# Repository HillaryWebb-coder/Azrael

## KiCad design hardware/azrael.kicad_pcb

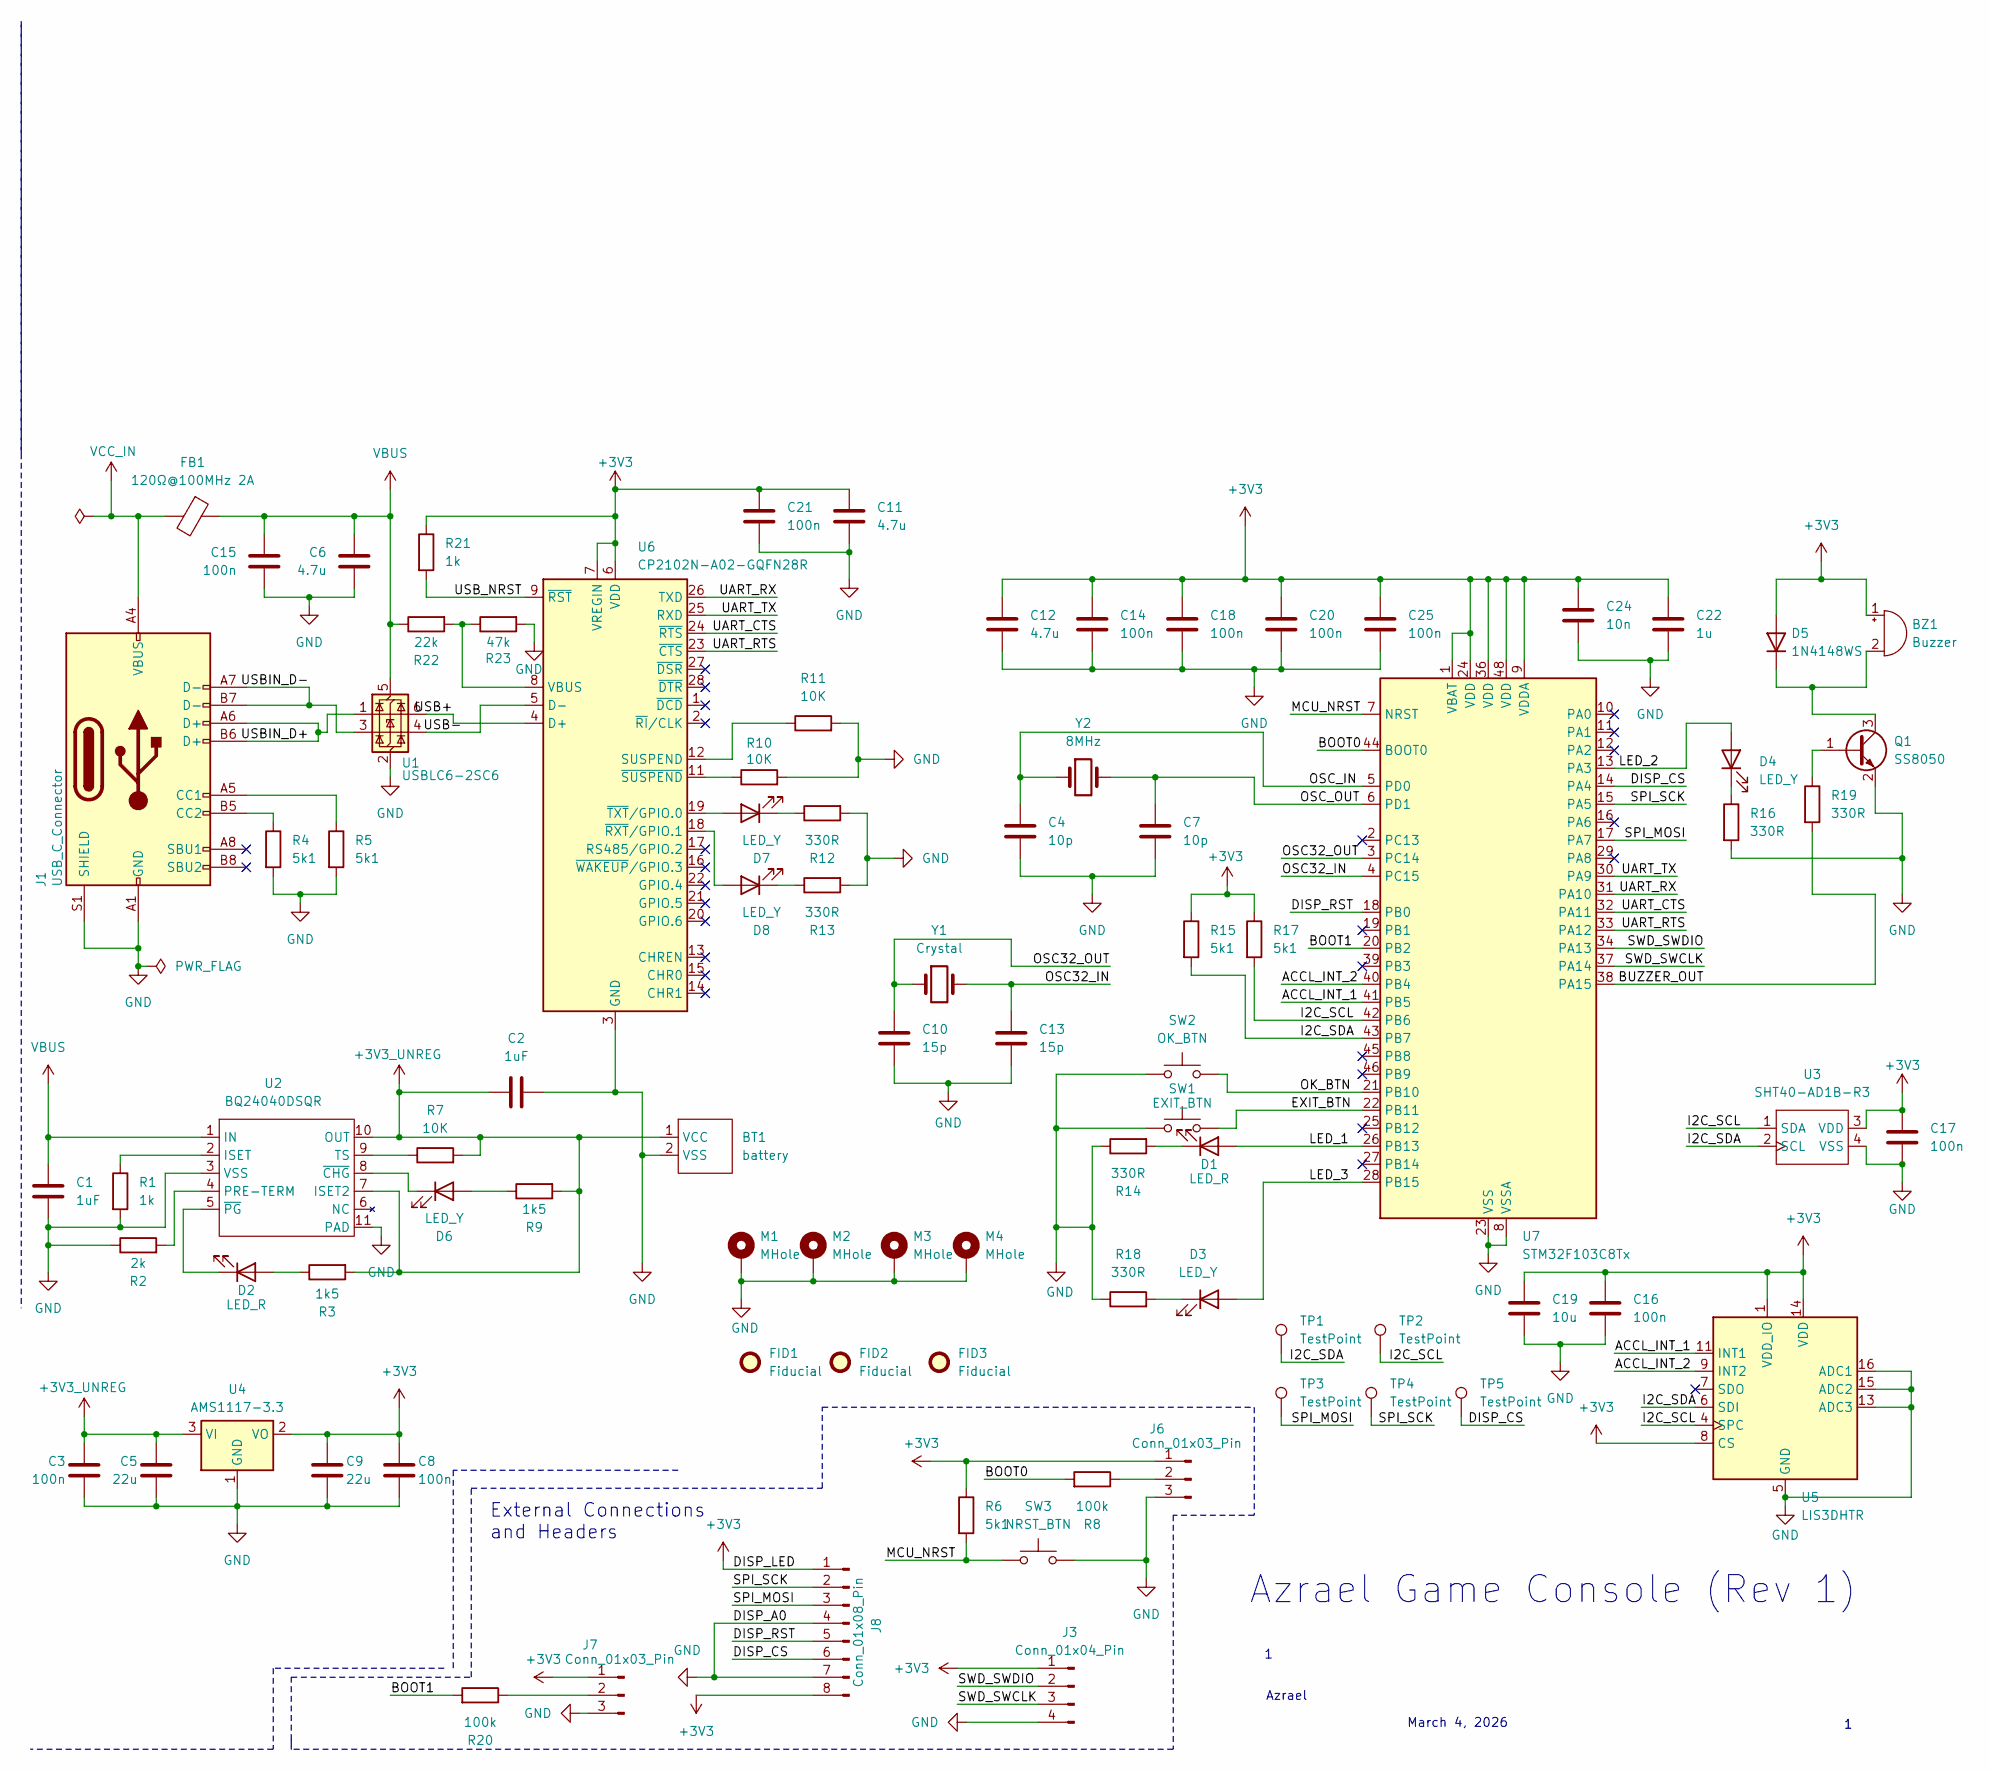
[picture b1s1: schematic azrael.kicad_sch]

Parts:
BT1: battery; SolderWire-0.5sqmm_1x02_P4.6mm_D0.9mm_OD2.1mm_Relief
BZ1: Buzzer; SolderWire-0.1sqmm_1x02_P3.6mm_D0.4mm_OD1mm_Relief
C1, C2: 1uF; C_0603_1608Metric_Pad1.08x0.95mm_HandSolder; MFR.Part # CL05A105KA5NQNC; JLCPCB Part # C52923
C3, C8, C14, C15, C16, C17, C18, C20, C21, C25: 100n; C_0402_1005Metric_Pad0.74x0.62mm_HandSolder; MFR.Part # CL05B104KO5NNNC; JLCPCB Part # C1525
C4, C7: 10p; C_0603_1608Metric_Pad1.08x0.95mm_HandSolder; MFR.Part # CL10C100JB8NNNC; JLCPCB Part # C1634
C5, C9: 22u; C_1206_3216Metric_Pad1.33x1.80mm_HandSolder; MFR.Part # CL31A226KAHNNNE; JLCPCB Part # C12891
C6, C11, C12: 4.7u; C_0805_2012Metric_Pad1.18x1.45mm_HandSolder; MFR.Part # CL21A475KAQNNNE; JLCPCB Part # C1779
C10, C13: 15p; C_0603_1608Metric_Pad1.08x0.95mm_HandSolder; MFR.Part # CL10C150JB8NNNC; JLCPCB Part # C1644
C19: 10u; C_0603_1608Metric_Pad1.08x0.95mm_HandSolder; MFR.Part # CL10A106MA8NRNC; JLCPCB Part # C96446
C22: 1u; C_0603_1608Metric_Pad1.08x0.95mm_HandSolder; MFR.Part # CL05A105KA5NQNC; JLCPCB Part # C52923
C24: 10n; C_0805_2012Metric_Pad1.18x1.45mm_HandSolder; MFR.Part # CL21B103KBANNNC; JLCPCB Part # C1710
D1, D2: LED_R; LED_0603_1608Metric_Pad1.05x0.95mm_HandSolder; MFR.Part # KT-0603R; JLCPCB Part # C2286
D3, D7, D8: LED_Y; LED_0805_2012Metric_Pad1.15x1.40mm_HandSolder; MFR.Part # KT-0805Y; JLCPCB Part # C2296
D4, D6: LED_Y; LED_0805_2012Metric_Pad1.15x1.40mm_HandSolder; MFR.Part # KT-0805G; JLCPCB Part # C2297
D5: 1N4148WS; D_SOD-323; MFR.Part # 1N4148WS; JLCPCB Part # C2128
FB1: 120Ω@100MHz 2A; L_0603_1608Metric; MFR.Part # BLM18PG121SN1D; JLCPCB Part # C14709
FID1, FID2, FID3: Fiducial; Fiducial_1.5mm_Mask3mm
J1: USB_C_Connector; USB_C_Receptacle_GCT_USB4105-xx-A_16P_TopMnt_Horizontal; MFR.Part # TYPE-C 16PIN 2MD(073); JLCPCB Part # C2765186
J3: Conn_01x04_Pin; JST_PH_B4B-PH-K_1x04_P2.00mm_Vertical
J6, J7: Conn_01x03_Pin; PinHeader_1x03_P2.54mm_Vertical
J8: Conn_01x08_Pin; JST_PH_B8B-PH-K_1x08_P2.00mm_Vertical
M1, M2, M3, M4: MHole; MountingHole_3.2mm_M3_Pad_Via
Q1: SS8050; SOT-23; MFR.Part # SS8050(RANGE:200-350); JLCPCB Part # C2150
R1, R21: 1k; R_0603_1608Metric_Pad0.98x0.95mm_HandSolder; MFR.Part # 0603WAF1001T5E; JLCPCB Part # C21190
R2: 2k; R_0603_1608Metric_Pad0.98x0.95mm_HandSolder; MFR.Part # 0603WAF2001T5E; JLCPCB Part # C22975
R3, R9: 1k5; R_0603_1608Metric_Pad0.98x0.95mm_HandSolder; MFR.Part # 0603WAF1501T5E; JLCPCB Part # C22843
R4, R5, R6, R15, R17: 5k1; R_0603_1608Metric_Pad0.98x0.95mm_HandSolder; MFR.Part # 0603WAF5101T5E; JLCPCB Part # C23186
R7, R10, R11: 10K; R_0603_1608Metric_Pad0.98x0.95mm_HandSolder; MFR.Part # 0603WAF1002T5E; JLCPCB Part # C25804
R8, R20: 100k; R_0603_1608Metric_Pad0.98x0.95mm_HandSolder; MFR.Part # 0603WAF1003T5E; JLCPCB Part # C25803
R12, R13, R14, R16, R18, R19: 330R; R_0603_1608Metric_Pad0.98x0.95mm_HandSolder; MFR.Part # 0603WAF3300T5E; JLCPCB Part # C23138
R22: 22k; R_0603_1608Metric_Pad0.98x0.95mm_HandSolder; MFR.Part # 0603WAF2202T5E; JLCPCB Part # C31850
R23: 47k; R_0603_1608Metric_Pad0.98x0.95mm_HandSolder; MFR.Part # 0603WAF4702T5E; JLCPCB Part # C25819
SW1: EXIT_BTN; SW_Push_SPST_NO_Alps_SKRK; MFR.Part # TS-1088-AR02016; JLCPCB Part # C720477
SW2: OK_BTN; SW_Push_SPST_NO_Alps_SKRK; MFR.Part # TS-1088-AR02016; JLCPCB Part # C720477
SW3: NRST_BTN; SW_Push_SPST_NO_Alps_SKRK; MFR.Part # TS-1088-AR02016; JLCPCB Part # C720477
TP1, TP2, TP3, TP4, TP5: TestPoint; TestPoint_Pad_D1.0mm
U1: USBLC6-2SC6; SOT-23-6
U2: BQ24040DSQR; Texas_DSQ0010A_WSON-10-1EP_2x2mm_P0.4mm_EP0.9x1.5mm_Thermal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; MFR.Part # BQ24040DSQR; JLCPCB Part # C81080
U3: SHT40-AD1B-R3; Sensirion_DFN-4_1.5x1.5mm_P0.8mm_SHT4x_NoCentralPad; MFR.Part # SHT40-AD1B-R3; JLCPCB Part # C2848306
U4: AMS1117-3.3; SOT-223-3_TabPin2; MFR.Part # AMS1117-3.3; JLCPCB Part # C6186
U5: LIS3DHTR; LGA-16_3x3mm_P0.5mm_LayoutBorder3x5y; MFR.Part # LIS3DHTR; JLCPCB Part # C15134
U6: CP2102N-A02-GQFN28R; QFN-28-1EP_5x5mm_P0.5mm_EP3.35x3.35mm; MFR.Part # CP2102N-A02-GQFN28R; JLCPCB Part # C964632
U7: STM32F103C8Tx; LQFP-48_7x7mm_P0.5mm
Y1: Crystal; Crystal_SMD_3215-2Pin_3.2x1.5mm; MFR.Part # Q13FC13500004; JLCPCB Part # C32346
Y2: 8MHz; Crystal_SMD_5032-2Pin_5.0x3.2mm_HandSoldering; MFR.Part # X50328MSB2GI; JLCPCB Part # C115962

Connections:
+3V3: BZ1.1 (+), C8.1, C9.1, C11.1, C12.1, C14.1, C16.1, C17.1, C18.1, C19.1, C20.1, C21.1, C22.1, C24.1, C25.1, D5.2 (A), J3.1, J6.1, J7.1, J8.1, J8.8, R6.1, R15.1, R17.1, R21.1, U3.3 (VDD), U4.2 (VO), U5.1 (VDD_IO), U5.8 (CS), U5.14 (VDD), U6.6 (VDD), U6.7 (VREGIN), U7.1 (VBAT), U7.9 (VDDA), U7.24 (VDD), U7.36 (VDD), U7.48 (VDD)
+3V3_UNREG: BT1.1 (VCC), C2.1, C3.1, C5.1, R3.2, R7.2, R9.2, U2.7 (ISET2), U2.10 (OUT), U4.3 (VI)
/ACCL_INT_1: U5.11 (INT1), U7.41 (PB5)
/ACCL_INT_2: U5.9 (INT2), U7.40 (PB4)
/BOOT0: R8.2, U7.44 (BOOT0)
/BOOT1: R20.2, U7.20 (PB2)
/BUZZER_OUT: R19.2, U7.38 (PA15)
/DISP_CS: J8.6, TP5.1, U7.14 (PA4)
/DISP_RST: J8.5, U7.18 (PB0)
/EXIT_BTN: SW1.2, U7.22 (PB11)
/I2C_SCL: R17.2, TP2.1, U3.1 (SDA), U5.4 (SPC), U7.42 (PB6)
/I2C_SDA: R15.2, TP1.1, U3.2 (SCL), U5.6 (SDI), U7.43 (PB7)
/LED_1: D1.2 (A), U7.26 (PB13)
/LED_2: D4.2 (A), U7.13 (PA3)
/LED_3: D3.2 (A), U7.28 (PB15)
/MCU_NRST: R6.2, SW3.1, U7.7 (NRST)
/OK_BTN: SW2.2, U7.21 (PB10)
/OSC32_IN: C13.1, U7.4 (PC15), Y1.2
/OSC32_OUT: C10.1, U7.3 (PC14), Y1.1
/OSC_IN: C4.1, U7.5 (PD0), Y2.1
/OSC_OUT: C7.1, U7.6 (PD1), Y2.2
/SPI_MOSI: J8.3, TP3.1, U7.17 (PA7)
/SPI_SCK: J8.2, TP4.1, U7.15 (PA5)
/SWD_SWCLK: J3.3, U7.37 (PA14)
/SWD_SWDIO: J3.2, U7.34 (PA13)
/UART_CTS: U6.24 (~RTS), U7.32 (PA11)
/UART_RTS: U6.23 (~CTS), U7.33 (PA12)
/UART_RX: U6.26 (TXD), U7.31 (PA10)
/UART_TX: U6.25 (RXD), U7.30 (PA9)
/USB+: U1.6 (I/O1), U6.4 (D+)
/USB-: U1.4 (I/O2), U6.5 (D-)
/USBIN_D+: J1.A6 (D+), J1.B6 (D+), U1.1 (I/O1)
/USBIN_D-: J1.A7 (D-), J1.B7 (D-), U1.3 (I/O2)
/USB_NRST: R21.2, U6.9 (~RST)
GND: BT1.2 (VSS), C1.2, C2.2, C3.2, C4.2, C5.2, C6.2, C7.2, C8.2, C9.2, C10.2, C11.2, C12.2, C13.2, C14.2, C15.2, C16.2, C17.2, C18.2, C19.2, C20.2, C21.2, C22.2, C24.2, C25.2, J1.A1 (GND), J1.A12 (GND), J1.B1 (GND), J1.B12 (GND), J1.S1 (SHIELD), J3.4, J6.3, J7.3, J8.4, J8.7, M1.1, M2.1, M3.1, M4.1, Q1.2 (E), R1.2, R2.1, R4.2, R5.2, R10.2, R11.2, R12.2, R13.2, R14.1, R16.2, R18.1, R23.2, SW1.1, SW2.1, SW3.2, U1.2 (GND), U2.3 (VSS), U2.11 (PAD), U3.4 (VSS), U4.1 (GND), U5.5 (GND), U5.10 (GND), U5.12 (GND), U5.13 (ADC3), U5.15 (ADC2), U5.16 (ADC1), U6.3 (GND), U6.29 (GND), U7.8 (VSSA), U7.23 (VSS), U7.35 (VSS), U7.47 (VSS)
unnamed: BZ1.2 (-), D5.1 (K), Q1.3 (C)
unnamed: D1.1 (K), R14.2
unnamed: D2.2 (A), R3.1
unnamed: D2.1 (K), U2.5 (~PG)
unnamed: D3.1 (K), R18.2
unnamed: D4.1 (K), R16.1
unnamed: D6.2 (A), R9.1
unnamed: D6.1 (K), U2.8 (~CHG)
unnamed: D7.2 (A), U6.19 (~TXT/GPIO.0)
unnamed: D7.1 (K), R12.1
unnamed: D8.2 (A), U6.18 (~RXT/GPIO.1)
unnamed: D8.1 (K), R13.1
unnamed: J1.A5 (CC1), R5.1
unnamed: J1.B5 (CC2), R4.1
unnamed: J6.2, R8.1
unnamed: J7.2, R20.1
unnamed: Q1.1 (B), R19.1
unnamed: R1.1, U2.2 (ISET)
unnamed: R2.2, U2.4 (PRE-TERM)
unnamed: R7.1, U2.9 (TS)
unnamed: R11.1, U6.12 (SUSPEND)
unnamed: R22.2, R23.1, U6.8 (VBUS)
unnamed: R10.1, U6.11 (~SUSPEND)
VBUS: C1.1, C6.1, C15.1, FB1.1, R22.1, U1.5 (VBUS), U2.1 (IN)
VCC_IN: FB1.2, J1.A4 (VBUS), J1.A9 (VBUS), J1.B4 (VBUS), J1.B9 (VBUS)

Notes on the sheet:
Azrael
Azrael Game Console (Rev 1)
External Connections and Headers
March 4, 2026

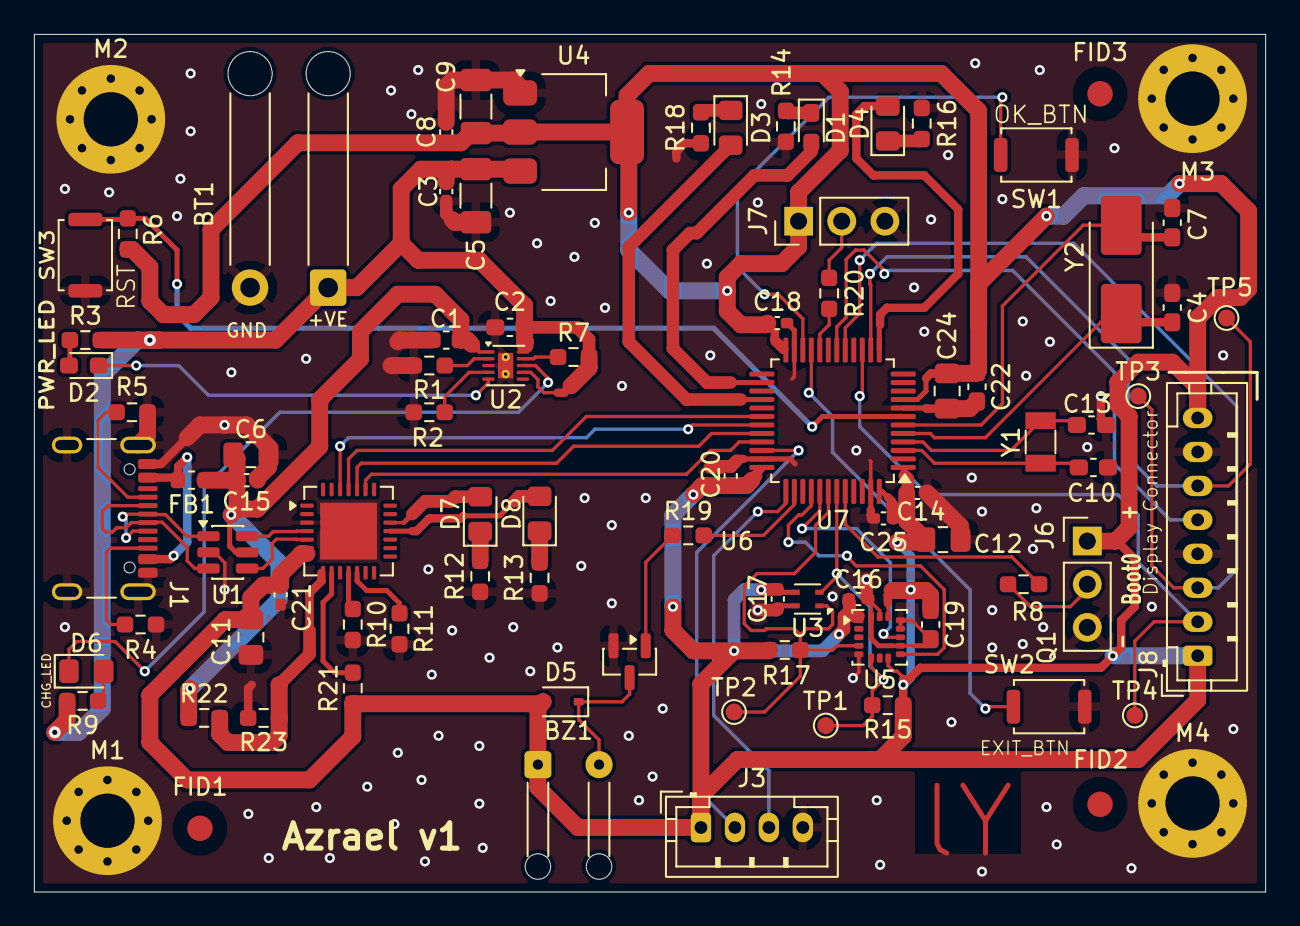
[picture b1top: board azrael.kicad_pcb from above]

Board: 2 copper layers, 72.5 x 50.5 mm, 88 parts (0 on the bottom side), 60 nets.

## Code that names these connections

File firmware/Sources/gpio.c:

#include "stm32f103xb.h"
#include "stm32f1xx.h"

#include "main.h"
#include "gpio.h"


void gpio_init(void)
{
   // Enable clocks for GPIOA, GPIOB, AFIO
   RCC->APB2ENR |= RCC_APB2ENR_IOPAEN   // GPIOA
                |  RCC_APB2ENR_IOPBEN;

    // PB15 - LED_3 - output push-pull
    // PB13 - LED_1 - output push-pull
    // PA3  - LED_2 - output push-pull
    // PB0  - DISP_RST - output push-pull
    // PB2  - DISP_DC  - output push-pull

   // Clear bits PB0, PB2
   GPIOB->CRL &= ~(GPIO_CRL_CNF0 | GPIO_CRL_MODE0 | GPIO_CRL_CNF2 | GPIO_CRL_MODE2);
    
   // clear bits PA3
   GPIOA->CRL &= ~(GPIO_CRL_CNF3 | GPIO_CRL_MODE3);

   // clear bits PB13, PB15
    GPIOB->CRH &= ~(GPIO_CRH_CNF13 | GPIO_CRH_MODE13 | GPIO_CRH_CNF15 | GPIO_CRH_MODE15);
    
    // Set PB0, PB2 as output push-pull, max speed 50 MHz
    GPIOB->CRL |= GPIO_CRL_MODE0 | GPIO_CRL_MODE2;

    // Set PA3 as output push-pull, max speed 50 MHz
    GPIOA->CRL |= GPIO_CRL_MODE3;

    // Set PB13, PB15 as output push-pull, max speed 50 MHz
    GPIOB->CRH |= GPIO_CRH_MODE13 | GPIO_CRH_MODE15;

    // PB11 - OK_BTN - input with pull-up
    // PB10 - EXIT_BTN - input with pull-up
    GPIOB->CRH &= ~(GPIO_CRH_CNF11 | GPIO_CRH_MODE11 | GPIO_CRH_CNF10 | GPIO_CRH_MODE10);
    GPIOB->CRH |= GPIO_CRH_CNF11_1 | GPIO_CRH_CNF10_1; // Input with pull-up/pull-down
    GPIOB->ODR |= (1 << OK_BTN_PIN) | (1 << EXIT_BTN_PIN); // Enable pull-up

    // Configure EXTI for PB11 and PB10
    AFIO->EXTICR[2] &= ~(AFIO_EXTICR3_EXTI11 | AFIO_EXTICR3_EXTI10); // Clear EXTI11 and EXTI10 bits

    AFIO->EXTICR[2] |= AFIO_EXTICR3_EXTI11_PB | AFIO_EXTICR3_EXTI10_PB; // Map EXTI11 and EXTI10 to PB

    // unmask EXTI11 and EXTI10
    EXTI->IMR |= (1 << 11) | (1 << 10);

    // Trigger on falling edge for both buttons
    EXTI->RTSR &= ~(1 << 11) | ~(1 << 10); // Disable rising edge trigger
    EXTI->FTSR |= (1 << 11) | (1 << 10);  // Enable falling edge trigger

    // Enable EXTI15_10_IRQn for PB11 and PB10
    NVIC_SetPriority(EXTI15_10_IRQn, 4);
    NVIC_EnableIRQ(EXTI15_10_IRQn);
}

void gpio_disp_dc_high(void)
{
	DISP_DC_GPIO->BSRR = (1U << DISP_DC_PIN);
}
void gpio_disp_dc_low(void)
{
	DISP_DC_GPIO->BRR = (1U << DISP_DC_PIN);
}
void gpio_disp_rst_high(void)
{
	DISP_RST_GPIO->BSRR = (1U << DISP_RST_PIN);
}
void gpio_disp_rst_low(void)
{
	DISP_RST_GPIO->BRR = (1U << DISP_RST_PIN);
}

extern EventGroupHandle_t xSystemFlags;

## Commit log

2026-05-28 Added kicad project, schematic and gerber files
2026-05-28 added initial firmware files, freeRTOS Implementation, SPI and ST7735 Display drivers
2026-06-01 Initialised I2C Peripheral and created the MVP AirRace game
2026-06-01 cleaned github repo
